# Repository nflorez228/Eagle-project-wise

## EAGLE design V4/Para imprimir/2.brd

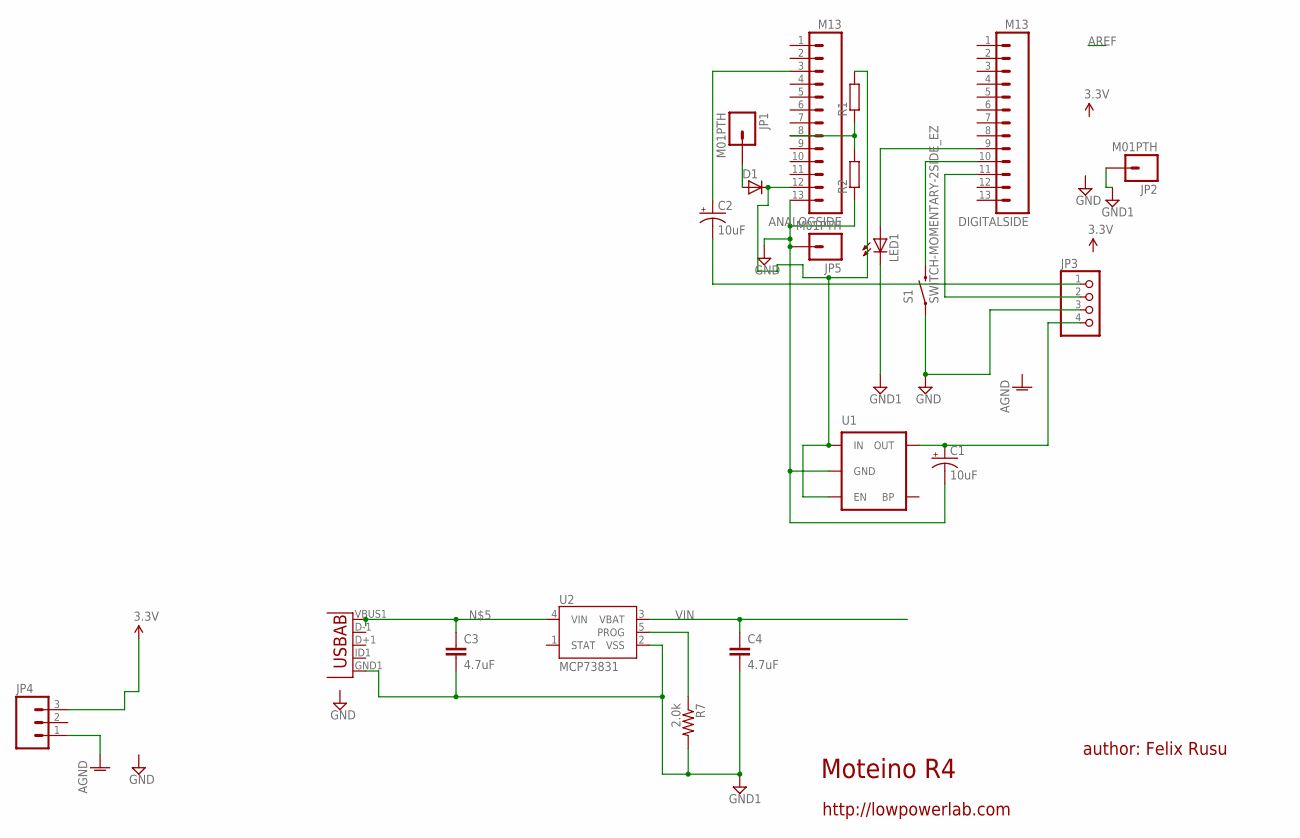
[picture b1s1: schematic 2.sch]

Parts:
ANALOGSIDE: M13; 1X13
C1, C2: 10uF; EIA3216
C3, C4: 4.7uF; 0603-CAP
D1: D-MLL-34; MELF-MLL34
DIGITALSIDE: M13; 1X13
JP1, JP2, JP5: M01PTH; 1X01
JP3: PINHD-1X4; 1X04
JP4: M03PTH; 1X03
JP9: Micro USB; USB-AB-MICRO-SMD_V03
LED1: LED3MM
R1, R2: R-EU_0204/7; 0204/7
R7: 2.0k; 0603-RES
S1: SWITCH-MOMENTARY-2SIDE_EZ; TACTILE-PTH-SIDEEZ
U1: MIC52055V; SOT23-5@1
U2: MCP73831; SOT23-5

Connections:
AGND: JP4.1
GND: ANALOGSIDE.13, C1.C (-), JP3.3, JP5.1, R2.1, S1.1, U1.2 (GND)
GND1: C3.2, C4.2, JP2.1, JP9.GND1 (GND), LED1.K (C), R7.2, U2.2 (VSS)
unnamed: DIGITALSIDE.10, S1.2
unnamed: DIGITALSIDE.11, JP3.2
unnamed: C2.C (-), JP3.1
unnamed: ANALOGSIDE.3, C2.A (+)
unnamed: ANALOGSIDE.12, C3.1, D1.1 (C), JP9.VBUS1 (VBUS), R1.2, U1.1 (IN), U1.3 (EN), U2.4 (VIN)
unnamed: ANALOGSIDE.8, R1.1, R2.2
unnamed: DIGITALSIDE.9, LED1.A
unnamed: D1.2 (A), JP1.1
unnamed: C1.A (+), JP3.4, U1.5 (OUT)
PROG: R7.1, U2.5 (PROG)
VCC: JP4.3
VIN: C4.1, U2.3 (VBAT)

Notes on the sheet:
Moteino R4
author: Felix Rusu
http://lowpowerlab.com

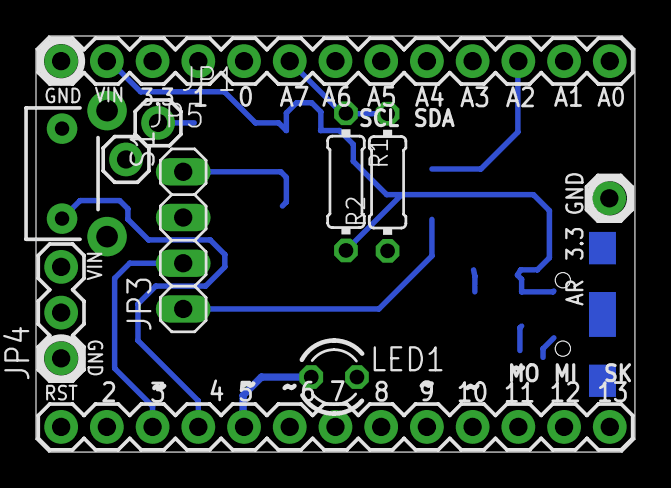
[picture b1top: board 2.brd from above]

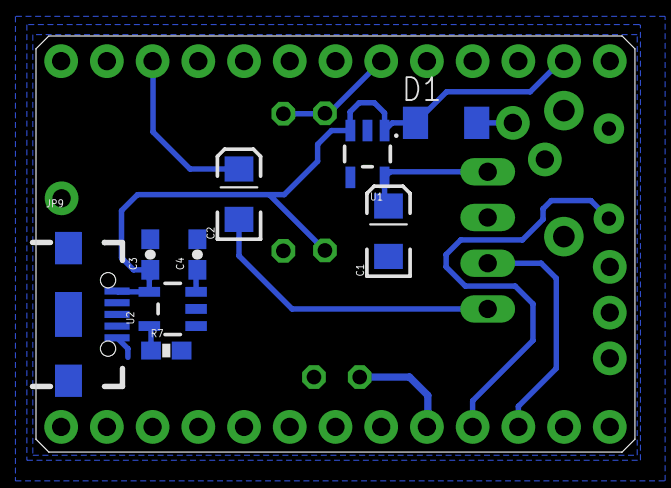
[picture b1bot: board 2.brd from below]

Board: 2 copper layers, 33.3 x 23.1 mm, 20 parts (9 on the bottom side), 13 nets.

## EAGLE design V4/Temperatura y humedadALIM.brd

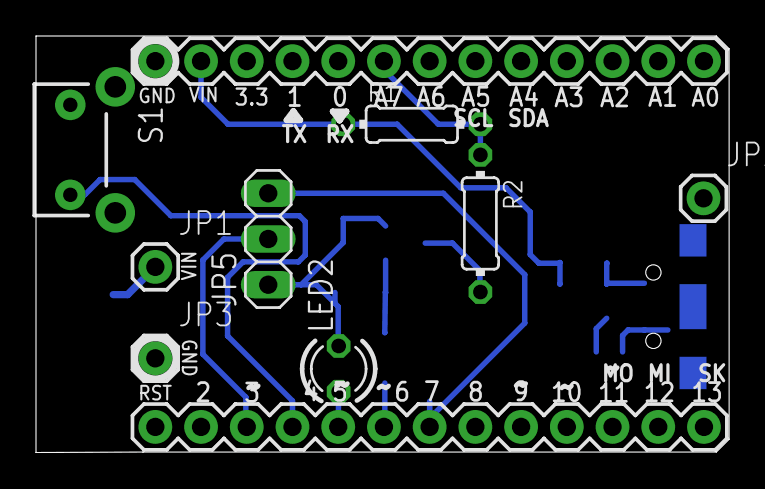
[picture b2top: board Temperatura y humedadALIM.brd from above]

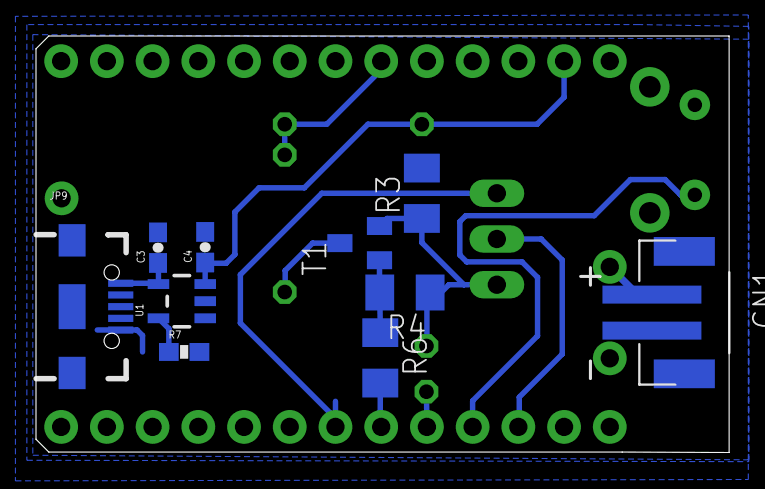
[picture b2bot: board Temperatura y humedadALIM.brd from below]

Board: 2 copper layers, 38.5 x 23.1 mm, 20 parts (10 on the bottom side), 16 nets.

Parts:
ANALOGSIDE: M13; 1X13
C3, C4: 4.7uF; 0603-CAP
CN1: JST-PH-2-SMT
DIGITALSIDE: M13; 1X13
JP1, JP2, JP3: M01PTH; 1X01
JP5: 1X03
JP9: Micro USB; USB-AB-MICRO-SMD_V03
LED2: LED3MM
R1, R2: 0204/7
R3, R4, R6: M1206
R7: 2.0k; 0603-RES
S1: SWITCH-MOMENTARY-2SIDE_EZ; TACTILE-PTH-SIDEEZ
T1: BC850; SOT23
U1: MCP73831; SOT23-5

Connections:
AGND: CN1.2, JP3.1
GND: ANALOGSIDE.13, R3.2, S1.1
GND1: C3.2, C4.2, JP2.1, JP9.GND1, R7.2, U1.2
unnamed: DIGITALSIDE.10, S1.2
unnamed: DIGITALSIDE.11, JP5.2
unnamed: DIGITALSIDE.7, JP5.3
unnamed: JP5.1, LED2.K, R3.1, R4.1, T1.2
unnamed: C3.1, JP9.VBUS1, U1.4
unnamed: ANALOGSIDE.8, R1.2, R2.1
unnamed: R2.2, T1.3
unnamed: R4.2, R6.1, T1.1
unnamed: DIGITALSIDE.8, R6.2
unnamed: DIGITALSIDE.9, LED2.A
PROG: R7.1, U1.5
VCC: CN1.1, JP1.1
VIN: ANALOGSIDE.12, C4.1, R1.1, U1.3

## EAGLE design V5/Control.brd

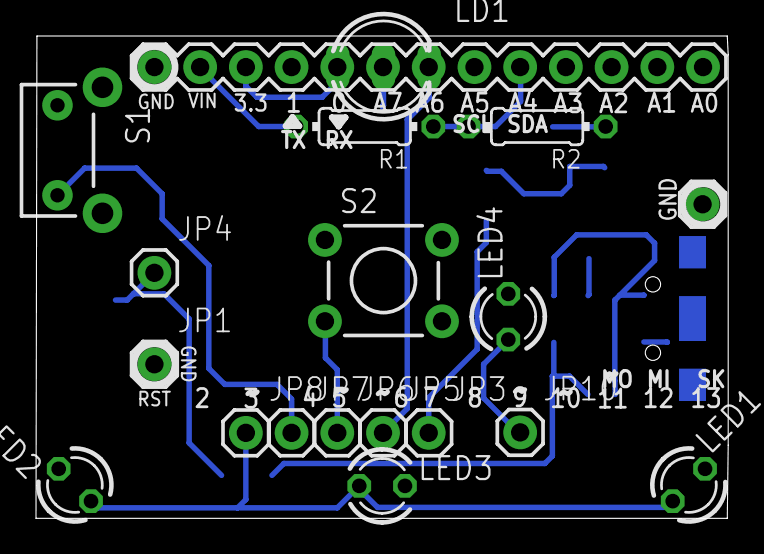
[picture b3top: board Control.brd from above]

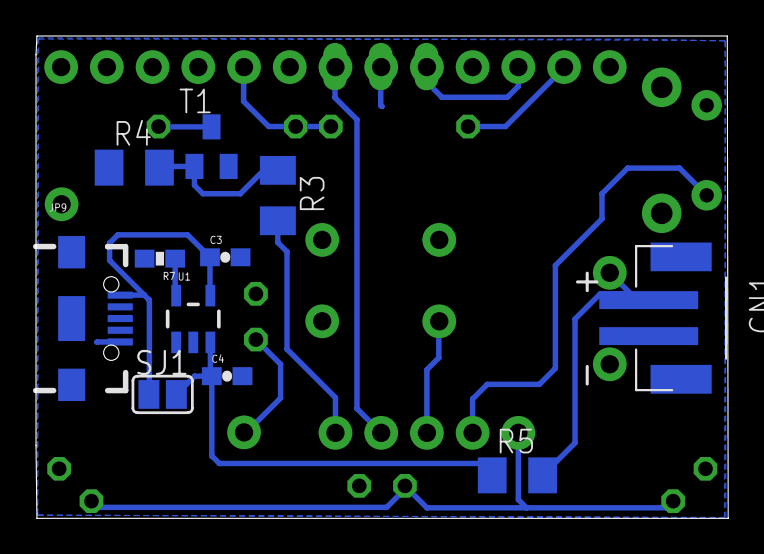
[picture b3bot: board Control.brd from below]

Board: 2 copper layers, 38.5 x 26.8 mm, 30 parts (11 on the bottom side), 17 nets.

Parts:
ANALOGSIDE: M13; 1X13
C3, C4: 4.7uF; 0603-CAP
CN1: JST-PH-2-SMT
JP1, JP2, JP3, JP4, JP5, JP6, JP7, JP8, JP10: M01PTH; 1X01
JP9: Micro USB; USB-AB-MICRO-SMD_V03
LD1: DUOLED-A-5MM
LED1, LED2, LED3, LED4: LED3MM
R1, R2: 0204/7
R3, R4, R5: M1206
R7: 2.0k; 0603-RES
S1: SWITCH-MOMENTARY-2SIDE_EZ; TACTILE-PTH-SIDEEZ
S2: TACTILE-PTH
SJ1: SJ
T1: BC850; SOT23
U1: MCP73831; SOT23-5

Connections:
AGND: CN1.2, JP1.1, LED2.K
GND: ANALOGSIDE.13, C3.2, C4.2, JP2.1, JP9.GND1, LD1.A, LED1.K, LED3.K, LED4.K, R4.1, R7.2, S1.1, S2.1, S2.2, T1.2, U1.2
unnamed: JP7.1, S1.2
unnamed: JP8.1, LED1.A, LED2.A, LED3.A
unnamed: JP6.1, S2.3
unnamed: JP5.1, LD1.CR
unnamed: C3.1, JP9.VBUS1, SJ1.1, U1.4
unnamed: ANALOGSIDE.5, R1.1, R2.2
unnamed: C4.1, R5.1, SJ1.2, U1.3
unnamed: ANALOGSIDE.12, R1.2
unnamed: JP3.1, R3.2
unnamed: R2.1, T1.3
unnamed: R3.1, R4.2, T1.1
unnamed: ANALOGSIDE.11, LD1.CX
unnamed: JP10.1, LED4.A
PROG: R7.1, U1.5
VCC: CN1.1, JP4.1, R5.2

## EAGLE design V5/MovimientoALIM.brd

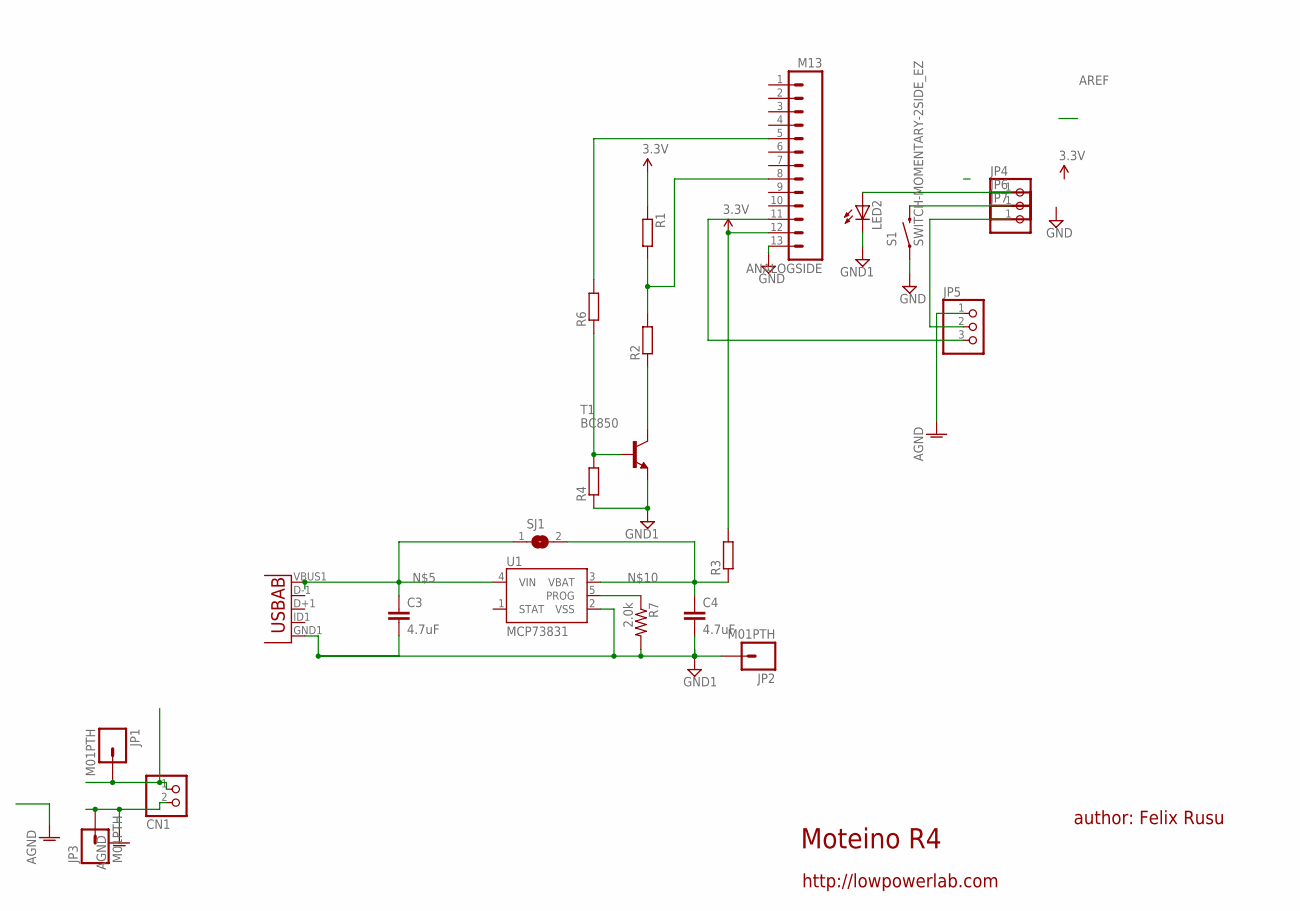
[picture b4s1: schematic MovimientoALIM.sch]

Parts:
ANALOGSIDE: M13; 1X13
C3, C4: 4.7uF; 0603-CAP
CN1: JST_2PIN-SMT; JST-PH-2-SMT
JP1, JP2, JP3: M01PTH; 1X01
JP4, JP6, JP7: PINHD-1X1; 1X01
JP5: PINHD-1X3; 1X03
JP9: Micro USB; USB-AB-MICRO-SMD_V03
LED2: LED3MM
R1, R2: R-EU_0204/7; 0204/7
R3, R4, R6: R-EU_M1206; M1206
R7: 2.0k; 0603-RES
S1: SWITCH-MOMENTARY-2SIDE_EZ; TACTILE-PTH-SIDEEZ
SJ1: SJ
T1: BC850; SOT23
U1: MCP73831; SOT23-5

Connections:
AGND: CN1.2 (1), JP3.1, JP5.1
GND: ANALOGSIDE.13, S1.1
GND1: C3.2, C4.2, JP2.1, JP9.GND1 (GND), LED2.K (C), R4.1, R7.2, T1.2 (E), U1.2 (VSS)
unnamed: JP6.1, S1.2
unnamed: JP5.2, JP7.1
unnamed: ANALOGSIDE.5, R6.2
unnamed: C3.1, JP9.VBUS1 (VBUS), SJ1.1, U1.4 (VIN)
unnamed: ANALOGSIDE.8, R1.2, R2.2
unnamed: R2.1, T1.3 (C)
unnamed: R4.2, R6.1, T1.1 (B)
unnamed: ANALOGSIDE.11, JP5.3
unnamed: C4.1, R3.1, SJ1.2, U1.3 (VBAT)
unnamed: JP4.1, LED2.A
unnamed: CN1.1 (2), JP1.1
PROG: R7.1, U1.5 (PROG)
VCC: ANALOGSIDE.12, R1.1, R3.2

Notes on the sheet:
Moteino R4
author: Felix Rusu
http://lowpowerlab.com

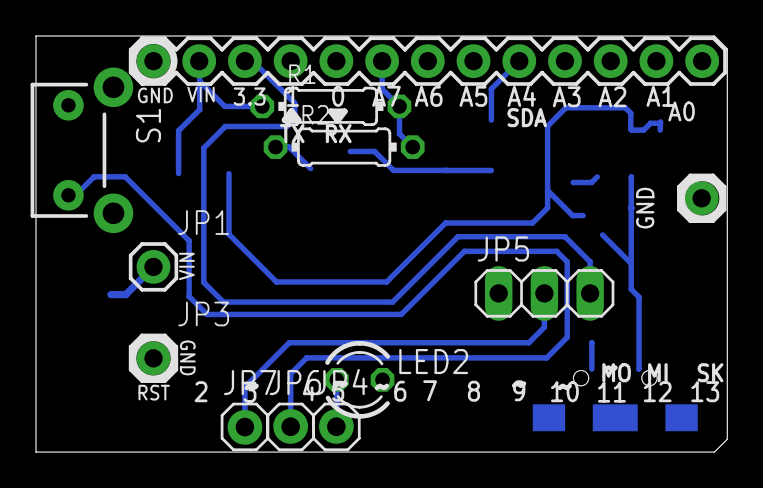
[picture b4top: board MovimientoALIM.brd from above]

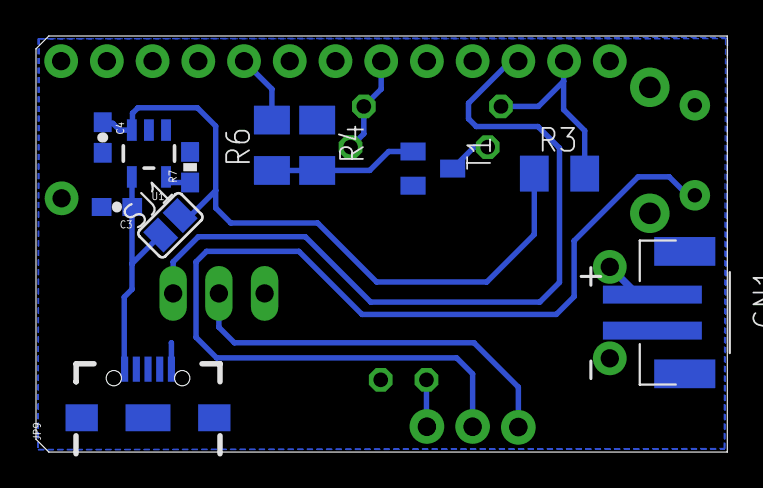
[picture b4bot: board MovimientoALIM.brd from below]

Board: 2 copper layers, 38.4 x 23.1 mm, 23 parts (11 on the bottom side), 16 nets.

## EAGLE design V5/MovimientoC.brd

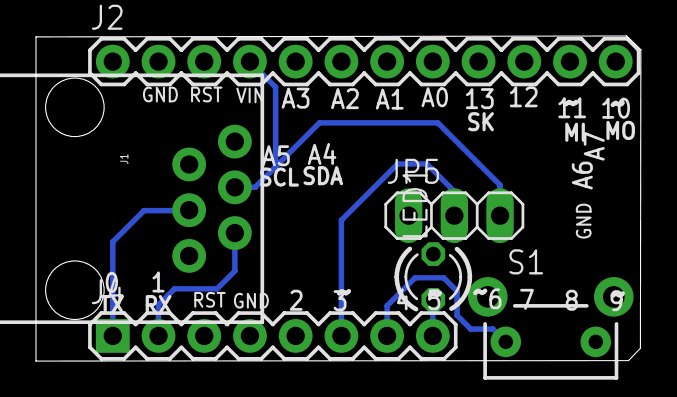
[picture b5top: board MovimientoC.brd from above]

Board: 2 copper layers, 33.6 x 18.1 mm, 6 parts (0 on the bottom side), 7 nets.

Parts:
J1: RJ11; RJ11-6
J2: 1X12
J4: 1X08
JP5: 1X03
LED1: LED3MM
S1: SWITCH-MOMENTARY-2SIDE_EZ; TACTILE-PTH-SIDEEZ

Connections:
GND: J1.1, J1.2, J2.2, J4.4, LED1.K, S1.2
unnamed: J4.7, S1.1
unnamed: J4.8, LED1.A
unnamed: J1.4, J4.1
unnamed: J1.5, J4.2
unnamed: J4.6, JP5.2
VIN: J1.3, J2.4, JP5.3

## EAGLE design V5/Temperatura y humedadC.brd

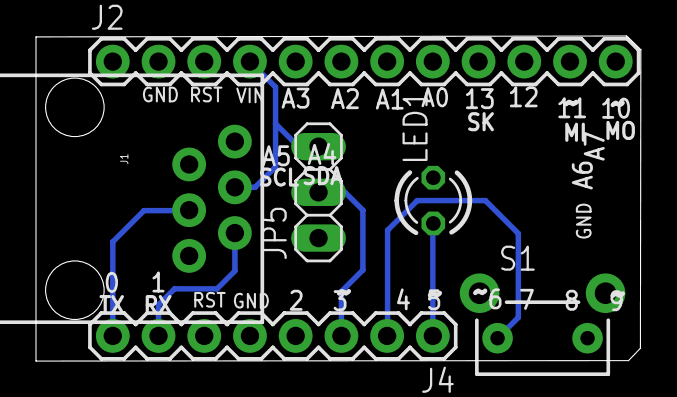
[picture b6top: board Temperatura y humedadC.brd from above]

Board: 2 copper layers, 33.6 x 18.1 mm, 6 parts (0 on the bottom side), 7 nets.

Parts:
J1: RJ11; RJ11-6
J2: 1X12
J4: 1X08_ROUND
JP5: 1X03
LED1: LED3MM
S1: SWITCH-MOMENTARY-2SIDE_EZ; TACTILE-PTH-SIDEEZ

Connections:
GND: J1.1, J1.2, J2.2, J4.5, JP5.1, LED1.K, S1.2
unnamed: J4.2, S1.1
unnamed: J4.1, LED1.A
unnamed: J1.4, J4.8
unnamed: J1.5, J4.7
unnamed: J4.3, JP5.2
VIN: J1.3, J2.4, JP5.3

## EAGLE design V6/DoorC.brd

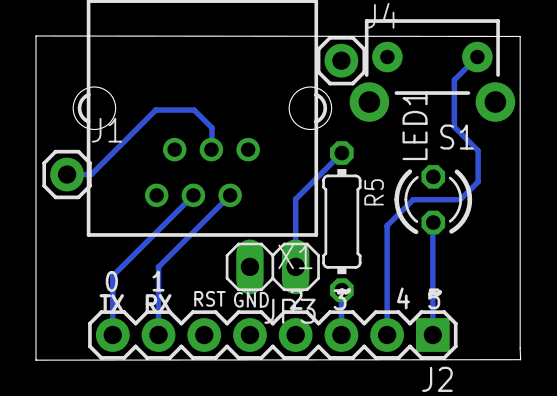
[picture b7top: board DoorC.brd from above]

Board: 2 copper layers, 26.9 x 18.0 mm, 8 parts (0 on the bottom side), 8 nets.

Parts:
J1, J4: 1X01
J2: 1X08
JP3: 1X02
LED1: LED3MM
R5: 0204/7
S1: SWITCH-MOMENTARY-2SIDE_EZ; TACTILE-PTH-SIDEEZ
X1: YH-55-10

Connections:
GND: J2.5, LED1.K, S1.2, X1.5
unnamed: J2.2, S1.1
unnamed: JP3.1, R5.1
unnamed: J2.1, LED1.A
unnamed: J2.8, X1.4
unnamed: J2.7, X1.2
unnamed: J2.3, R5.2
VIN: J1.1, X1.3

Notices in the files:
parts and their libraries:
SparkFun-Connectors: Licensing: CC v3.0 Share-Alike You are welcome to use this library for commercial purposes.
SparkFun-Electromechanical: Licensing: Creative Commons ShareAlike 4.0 International - https://creativecommons.org/licenses/by-sa/4.0
